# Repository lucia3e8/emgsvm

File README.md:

# Subvocal Recognition Colllar
Eventually, a neck-worn sEMG + neck microphone for near-subvocal speech recognition.

Currently, some prototypes

## Layout

```
.
├── adc # tests for a promising 8-channel ADC chip
├── afe # janky, INA128-based analog frontend
├── components # for KiCad
├── datasheets
├── piezo # preamp for a piezo mic
├── scripts # random nonsense
├── spice # analog circuit simulation
```

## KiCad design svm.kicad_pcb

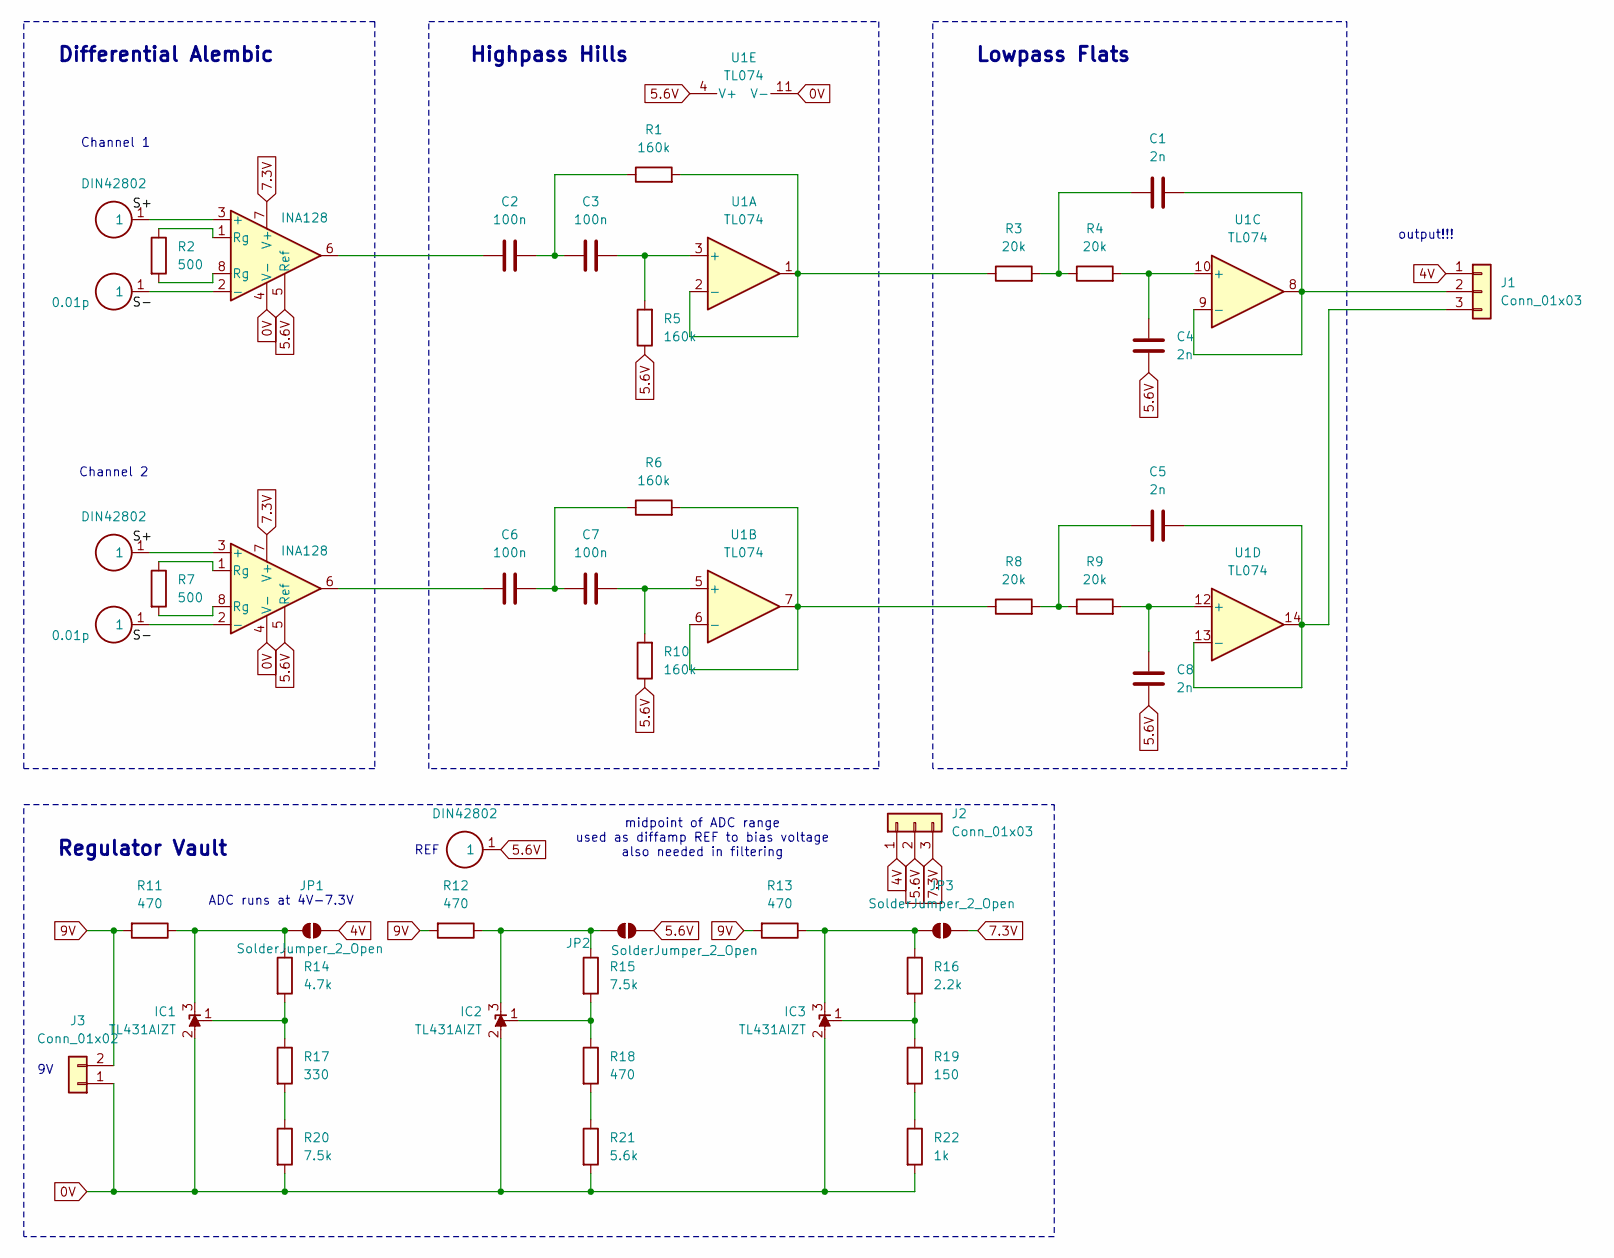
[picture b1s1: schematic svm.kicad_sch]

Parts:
C1, C4, C5, C8: 2n; C_Rect_L16.5mm_W4.7mm_P15.00mm_MKT
C2, C3, C6, C7: 100n; C_Rect_L7.2mm_W2.5mm_P5.00mm_FKS2_FKP2_MKS2_MKP2
IC1, IC2, IC3: TL431AIZT; Mouser Part Number 511-TL431AIZT
J1, J2: Conn_01x03; JST_XH_B3B-XH-A_1x03_P2.50mm_Vertical
J3: Conn_01x02; JST_XH_B2B-XH-A_1x02_P2.50mm_Vertical
JP1, JP2, JP3: SolderJumper_2_Open; SolderJumper-2_P1.3mm_Open_RoundedPad1.0x1.5mm
R1, R5, R6, R10: 160k; R_Axial_DIN0309_L9.0mm_D3.2mm_P12.70mm_Horizontal
R2, R7: 500; R_Axial_DIN0309_L9.0mm_D3.2mm_P12.70mm_Horizontal
R3, R4, R8, R9: 20k; R_Axial_DIN0309_L9.0mm_D3.2mm_P12.70mm_Horizontal
R11, R12, R13, R18: 470; R_Axial_DIN0309_L9.0mm_D3.2mm_P12.70mm_Horizontal
R14: 4.7k; R_Axial_DIN0309_L9.0mm_D3.2mm_P12.70mm_Horizontal
R15, R20: 7.5k; R_Axial_DIN0309_L9.0mm_D3.2mm_P12.70mm_Horizontal
R16: 2.2k; R_Axial_DIN0309_L9.0mm_D3.2mm_P12.70mm_Horizontal
R17: 330; R_Axial_DIN0309_L9.0mm_D3.2mm_P12.70mm_Horizontal
R19: 150; R_Axial_DIN0309_L9.0mm_D3.2mm_P12.70mm_Horizontal
R21: 5.6k; R_Axial_DIN0309_L9.0mm_D3.2mm_P12.70mm_Horizontal
R22: 1k; R_Axial_DIN0309_L9.0mm_D3.2mm_P12.70mm_Horizontal
S1, S3, S5: DIN42802; EMSLIFE EE-B04
S2, S4: 0.01p; EMSLIFE EE-B04
U1: TL074; TL074CN
U2, U3: INA128; INA128PA

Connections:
0V: IC1.2, IC2.2, IC3.2, J3.1, R20.2, R21.2, R22.2, U1.11 (V-), U2.4 (V-), U3.4 (V-)
4V: J1.1, J2.1, JP1.2 (B)
5.6V: C4.1, C8.1, J2.2, JP2.2 (B), R5.1, R10.1, S5.1, U1.4 (V+), U2.5 (Ref), U3.5 (Ref)
7.3V: J2.3, JP3.2 (B), U2.7 (V+), U3.7 (V+)
9V: J3.2, R11.2, R12.2, R13.2
unnamed: C1.1, R3.2, R4.1
unnamed: C2.1, U2.6
unnamed: C2.2, C3.1, R1.1
unnamed: C5.1, R8.2, R9.1
unnamed: C6.1, U3.6
unnamed: C6.2, C7.1, R6.1
unnamed: IC1.1, R14.2, R17.1
unnamed: IC2.1, R15.2, R18.1
unnamed: IC3.1, R16.2, R19.1
unnamed: C1.2, J1.2, U1.8, U1.9 (-)
unnamed: C5.2, J1.3, U1.13 (-), U1.14
unnamed: IC1.3, JP1.1 (A), R11.1, R14.1
unnamed: IC2.3, JP2.1 (A), R12.1, R15.1
unnamed: IC3.3, JP3.1 (A), R13.1, R16.1
unnamed: R2.1, U2.1 (Rg)
unnamed: R2.2, U2.8 (Rg)
unnamed: R7.1, U3.1 (Rg)
unnamed: R7.2, U3.8 (Rg)
unnamed: R17.2, R20.1
unnamed: R18.2, R21.1
unnamed: R19.2, R22.1
unnamed: C3.2, R5.2, U1.3 (+)
unnamed: R1.2, R3.1, U1.1, U1.2 (-)
unnamed: C7.2, R10.2, U1.5 (+)
unnamed: R6.2, R8.1, U1.6 (-), U1.7
unnamed: C4.2, R4.2, U1.10 (+)
unnamed: C8.2, R9.2, U1.12 (+)
unnamed: S1.1, U2.3 (+)
unnamed: S2.1, U2.2 (-)
unnamed: S3.1, U3.3 (+)
unnamed: S4.1, U3.2 (-)

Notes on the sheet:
Lowpass Flats
Channel 1
Regulator Vault
Channel 2
output!!!
REF
Differential Alembic
midpoint of ADC range used as diffamp REF to bias voltage also needed in filtering
ADC runs at 4V-7.3V
Highpass Hills

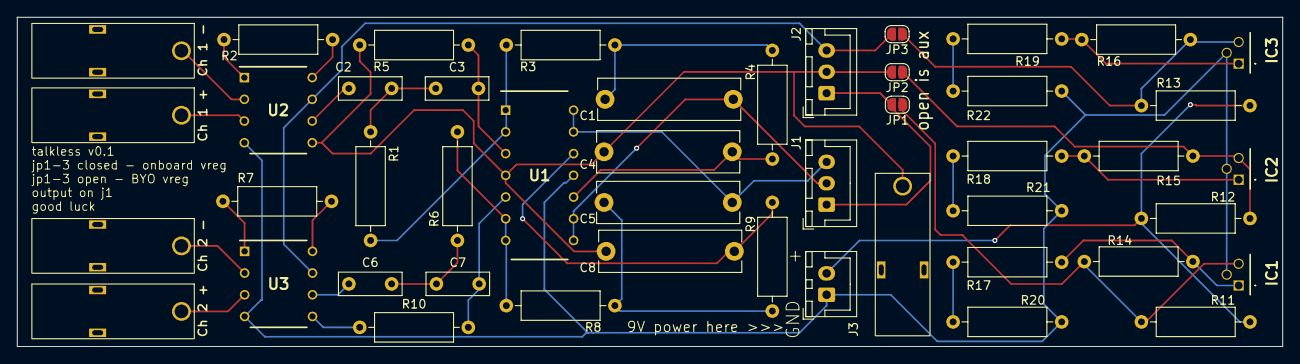
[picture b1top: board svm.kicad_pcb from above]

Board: 2 copper layers, 148.0 x 38.5 mm, 47 parts (0 on the bottom side), 36 nets.

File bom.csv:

"Reference","Value","Datasheet","Footprint","Qty","DNP"
"C1,C4,C5,C8","2n","~","Capacitor_THT:C_Rect_L16.5mm_W4.7mm_P15.00mm_MKT","4",""
"C2,C3,C6,C7","100n","~","-- mixed values --","4",""
"IC1,IC2,IC3","TL431AIZT","https://www.st.com/resource/en/datasheet/tl431.pdf","lucia:TL431AIZT","3",""
"J1,J2","Conn_01x03","~","Connector_JST:JST_XH_B3B-XH-A_1x03_P2.50mm_Vertical","2",""
"J3","Conn_01x02","~","Connector_JST:JST_XH_B2B-XH-A_1x02_P2.50mm_Vertical","1",""
"R1,R5,R6,R10","160k","~","Resistor_THT:R_Axial_DIN0309_L9.0mm_D3.2mm_P12.70mm_Horizontal","4",""
"R2,R7","500","~","Resistor_THT:R_Axial_DIN0309_L9.0mm_D3.2mm_P12.70mm_Horizontal","2",""
"R3,R4,R8,R9","20k","~","Resistor_THT:R_Axial_DIN0309_L9.0mm_D3.2mm_P12.70mm_Horizontal","4",""
"R11,R12,R13,R18","470","~","Resistor_THT:R_Axial_DIN0309_L9.0mm_D3.2mm_P12.70mm_Horizontal","4",""
"R14","4.7k","~","Resistor_THT:R_Axial_DIN0309_L9.0mm_D3.2mm_P12.70mm_Horizontal","1",""
"R15,R20","7.5k","~","Resistor_THT:R_Axial_DIN0309_L9.0mm_D3.2mm_P12.70mm_Horizontal","2",""
"R16","2.2k","~","Resistor_THT:R_Axial_DIN0309_L9.0mm_D3.2mm_P12.70mm_Horizontal","1",""
"R17","330","~","Resistor_THT:R_Axial_DIN0309_L9.0mm_D3.2mm_P12.70mm_Horizontal","1",""
"R19","150","~","Resistor_THT:R_Axial_DIN0309_L9.0mm_D3.2mm_P12.70mm_Horizontal","1",""
"R21","5.6k","~","Resistor_THT:R_Axial_DIN0309_L9.0mm_D3.2mm_P12.70mm_Horizontal","1",""
"R22","1k","~","Resistor_THT:R_Axial_DIN0309_L9.0mm_D3.2mm_P12.70mm_Horizontal","1",""
"S1,S3,S5","DIN42802","~","lucia:EMSLIFE EE-B04","3",""
"S2,S4","0.01p","~","lucia:EMSLIFE EE-B04","2",""
"U1","TL074","http://www.ti.com/lit/ds/symlink/tl071.pdf","lucia:TL074CN","1",""
"U2,U3","INA128","http://www.ti.com/lit/ds/symlink/ina128.pdf","lucia:INA128PA","2",""

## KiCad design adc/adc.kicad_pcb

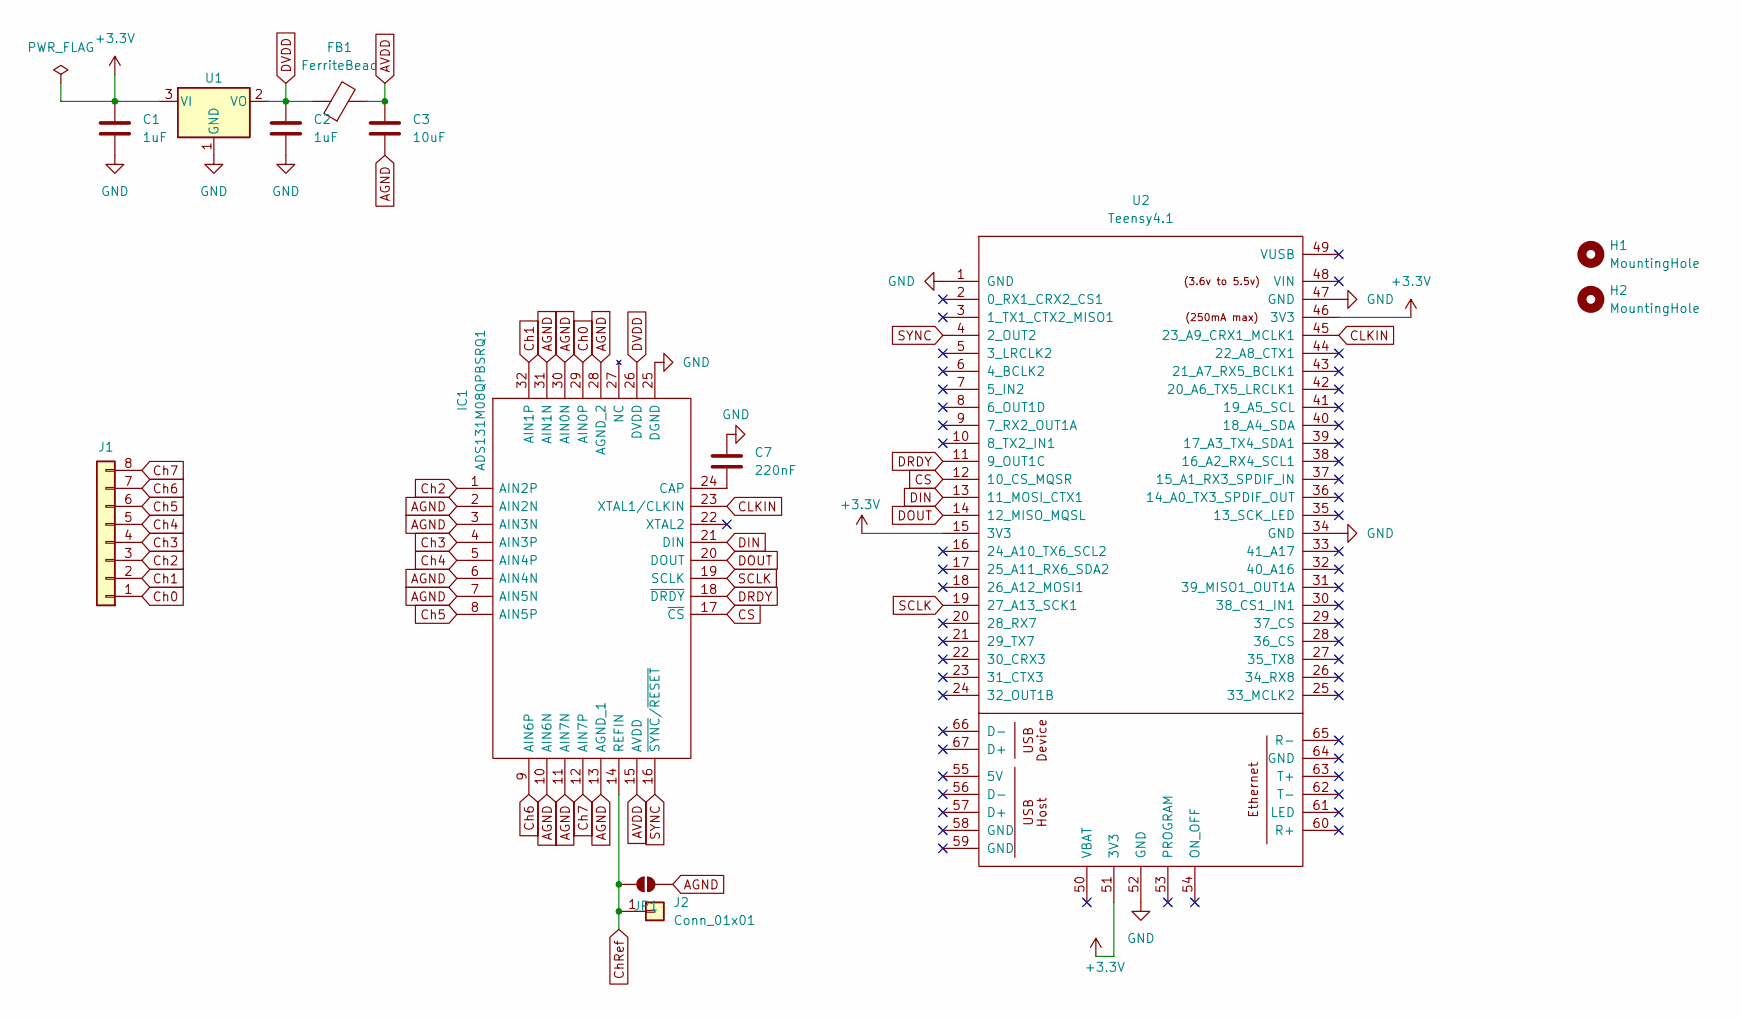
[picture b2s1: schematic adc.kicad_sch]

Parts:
C1, C2: 1uF; C_0402_1005Metric
C3: 10uF; C_0402_1005Metric
C7: 220nF; C_0402_1005Metric
FB1: FerriteBead; C_0402_1005Metric
H1, H2: MountingHole; MountingHole_2.7mm_M2.5
IC1: ADS131M08QPBSRQ1; QFP50P700X700X120-32N; Mouser Part Number 595-ADS131M08QPBSRQ1
J1: Conn_01x08; PinHeader_1x08_P2.54mm_Vertical
J2: Conn_01x01; PinHeader_1x01_P2.54mm_Vertical
JP1: SolderJumper_2_Open; SolderJumper-2_P1.3mm_Open_RoundedPad1.0x1.5mm
U1: MCP1700x-330xxTT; SOT-23
U2: Teensy4.1; Teensy41

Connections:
+3.3V: C1.1, U1.3 (VI), U2.15 (3V3), U2.46 (3V3), U2.51 (3V3)
AGND: C3.2, IC1.2 (AIN2N), IC1.3 (AIN3N), IC1.6 (AIN4N), IC1.7 (AIN5N), IC1.10 (AIN6N), IC1.11 (AIN7N), IC1.13 (AGND_1), IC1.28 (AGND_2), IC1.30 (AIN0N), IC1.31 (AIN1N), JP1.2 (B)
AVDD: C3.1, FB1.2, IC1.15 (AVDD)
CLKIN: IC1.23 (XTAL1/CLKIN), U2.45 (23_A9_CRX1_MCLK1)
CS: IC1.17 (~CS), U2.12 (10_CS_MQSR)
Ch0: IC1.29 (AIN0P), J1.1
Ch1: IC1.32 (AIN1P), J1.2
Ch2: IC1.1 (AIN2P), J1.3
Ch3: IC1.4 (AIN3P), J1.4
Ch4: IC1.5 (AIN4P), J1.5
Ch5: IC1.8 (AIN5P), J1.6
Ch6: IC1.9 (AIN6P), J1.7
Ch7: IC1.12 (AIN7P), J1.8
ChRef: IC1.14 (REFIN), J2.1, JP1.1 (A)
DIN: IC1.21 (DIN), U2.13 (11_MOSI_CTX1)
DOUT: IC1.20 (DOUT), U2.14 (12_MISO_MQSL)
DRDY: IC1.18 (~DRDY), U2.11 (9_OUT1C)
DVDD: C2.1, FB1.1, IC1.26 (DVDD), U1.2 (VO)
GND: C1.2, C2.2, C7.1, IC1.25 (DGND), U1.1 (GND), U2.1 (GND), U2.34 (GND), U2.47 (GND), U2.52 (GND)
unnamed: C7.2, IC1.24 (CAP)
SCLK: IC1.19 (SCLK), U2.19 (27_A13_SCK1)
SYNC: IC1.16 (~SYNC/~RESET), U2.4 (2_OUT2)

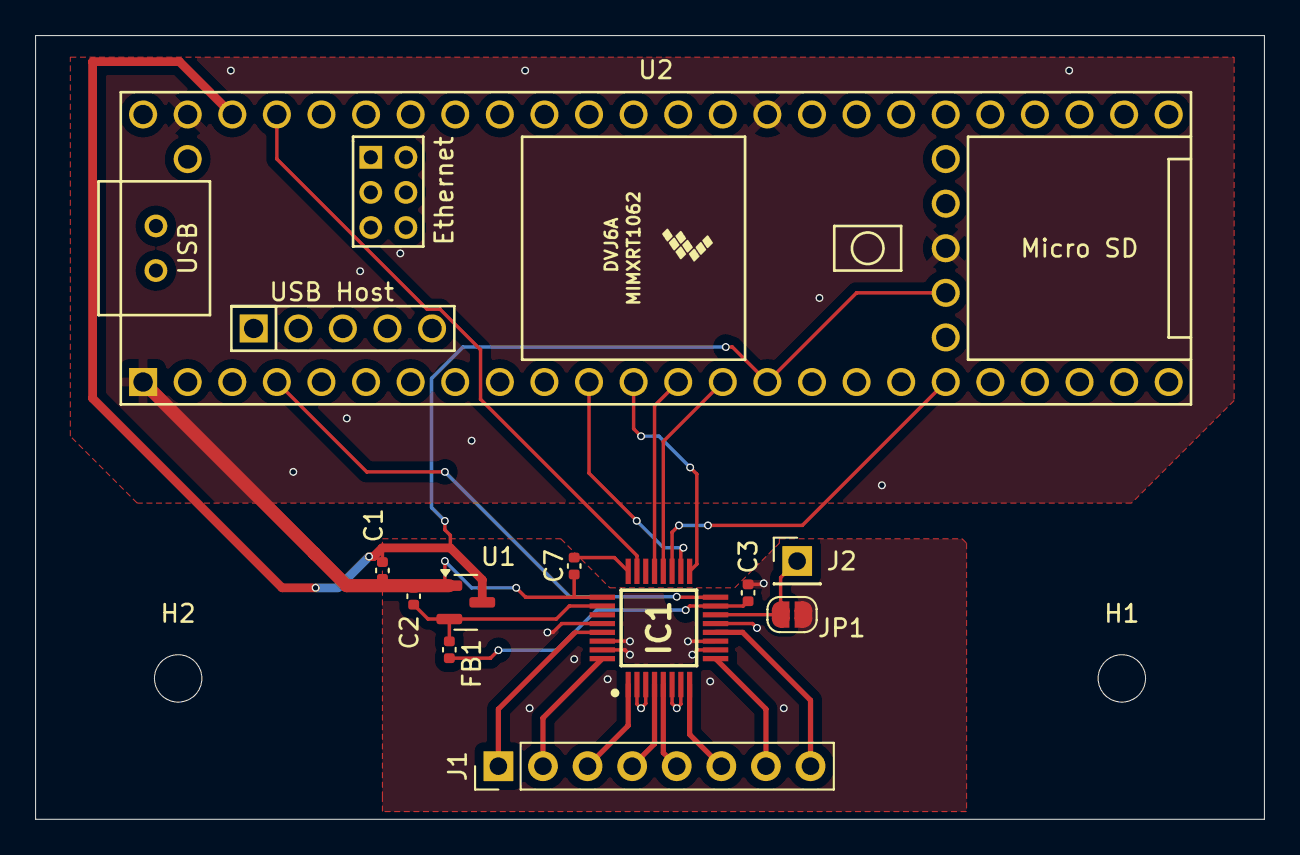
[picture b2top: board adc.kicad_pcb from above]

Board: 2 copper layers, 70.0 x 44.6 mm, 13 parts (0 on the bottom side), 22 nets.

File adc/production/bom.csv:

Designator,Footprint,Quantity,Value,LCSC Part #
"C1, C2",0402,2,1uF,
C3,0402,1,10uF,
C7,0402,1,220nF,
FB1,0402,1,FerriteBead,
IC1,QFP50P700X700X120-32N,1,ADS131M08QPBSRQ1,
J1,PinHeader_1x08_P2.54mm_Vertical,1,Conn_01x08,
J2,PinHeader_1x01_P2.54mm_Vertical,1,Conn_01x01,
U1,SOT-23,1,MCP1700x-330xxTT,
U2,Teensy41,1,Teensy4.1,

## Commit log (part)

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2025-02-07 v0 design
2025-02-10 uhh resistor finder script lol
2025-02-14 gitignore
2025-02-14 components
2025-02-14 spice models for analog fe
2025-02-14 cleanup
2025-02-14 schematic, placement and routing for analog FE pcb
2025-02-14 resistor matcher script
2025-02-18 add readme
2025-05-11 update gitignore
2025-05-11 kicad stuff
2025-05-13 working logs and pwm
2025-05-13 uncommit binary
2025-05-16 it workie :))) reads from ADC channels just fine, just had to pull SYNC up of COURSE
2025-05-17 data now logged over usb serial as base64, it's still reasonably simple but pretty compact
2025-05-23 fmt, also reg reads
2025-05-23 add host software (receives data from serial)
2025-05-23 less verbose
2025-05-26 unleashed claude code upon the visualizer and she did great
2025-06-14 show status register contents
2025-06-14 clean up repo a bit
2025-06-14 ads131m08 ADC breakout board
